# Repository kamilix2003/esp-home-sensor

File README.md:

# esp-home-sensor

Wireless ESP32-C6 based home environmental sensor powered by single Li-ion 18650 cell, running ESP home firmware optimized for battery life which is to be measured in months instead of days.

<figure style="text-align:center;">
  
</figure>

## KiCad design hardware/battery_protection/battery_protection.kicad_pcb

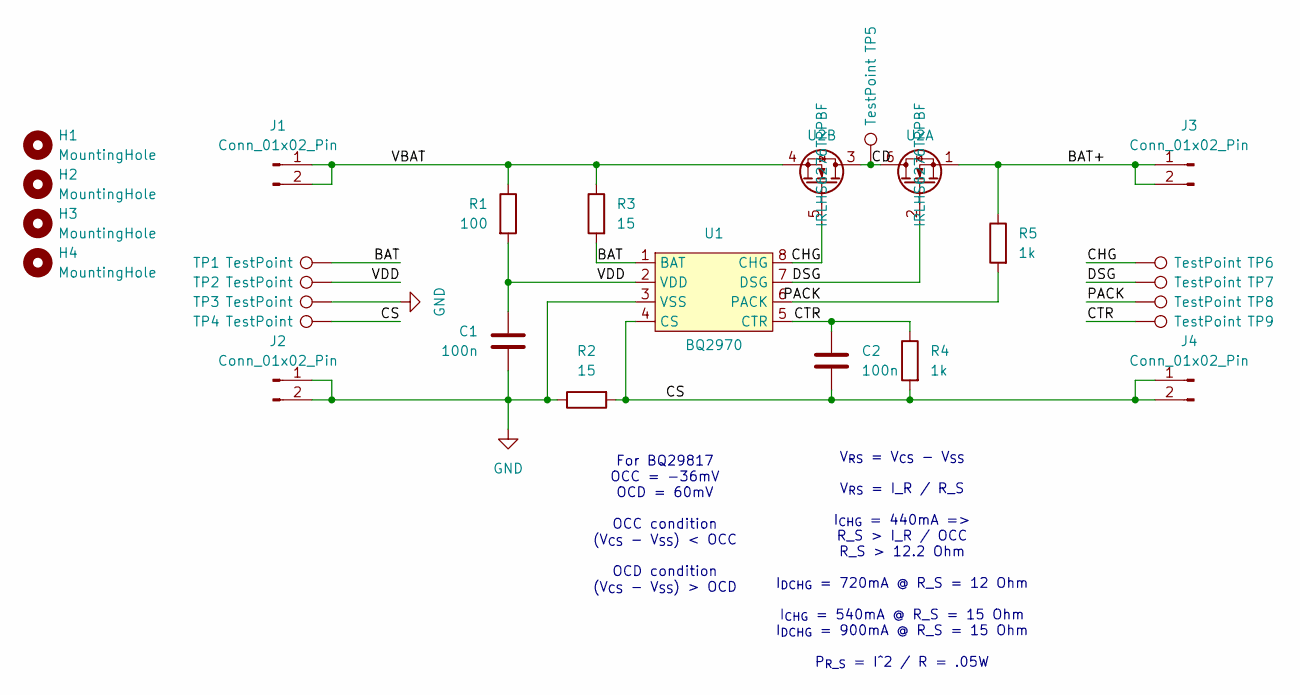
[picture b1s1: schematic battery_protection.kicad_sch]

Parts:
C1, C2: 100n; C_0402_1005Metric
H1, H2, H3, H4: MountingHole; MountingHole_2.2mm_M2
J1, J2, J3, J4: Conn_01x02_Pin; PinHeader_1x02_P2.54mm_Vertical
R1: 100; R_0402_1005Metric
R2, R3: 15; R_0402_1005Metric
R4, R5: 1k; R_0402_1005Metric
TP1, TP2, TP3, TP4, TP5, TP6, TP7, TP8, TP9: TestPoint; TestPoint_THTPad_D1.0mm_Drill0.5mm
U1: BQ2970; QFN-8_1.5x1.5_Pitch0.5mm
U2: IRLHS6276TRPBF; QFN-6_2x2_Pitch0.65mm

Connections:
/BAT: R3.2, TP1.1 (1_1), U1.1 (BAT)
/BAT+: J3.1, J3.2, R5.1, U2.1
/CD: TP5.1 (1_1), U2.3, U2.6
/CHG: TP6.1 (1_1), U1.8 (CHG), U2.5
/CS: C2.2, J4.1, J4.2, R2.2, R4.2, TP4.1 (1_1), U1.4 (CS)
/CTR: C2.1, R4.1, TP9.1 (1_1), U1.5 (CTR)
/DSG: TP7.1 (1_1), U1.7 (DSG), U2.2
/PACK: R5.2, TP8.1 (1_1), U1.6 (PACK)
/VBAT: J1.1, J1.2, R1.1, R3.1, U2.4
/VDD: C1.1, R1.2, TP2.1 (1_1), U1.2 (VDD)
GND: C1.2, J2.1, J2.2, R2.1, TP3.1 (1_1), U1.3 (VSS)

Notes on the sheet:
V_{RS} = V_{CS} - V_{SS} V_{RS} = I_R / R_S I_{CHG} = 440mA => R_S > I_R / OCC R_S > 12.2 Ohm I_{DCHG} = 720mA @ R_S = 12 Ohm I_{CHG} = 540mA @ R_S = 15 Ohm I_{DCHG} = 900mA @ R_S = 15 Ohm P_{R_S} = I^2 / R = .05W
For BQ29817 OCC = -36mV OCD = 60mV OCC condition (V_{CS} - V_{SS}) < OCC OCD condition (V_{CS} - V_{SS}) > OCD

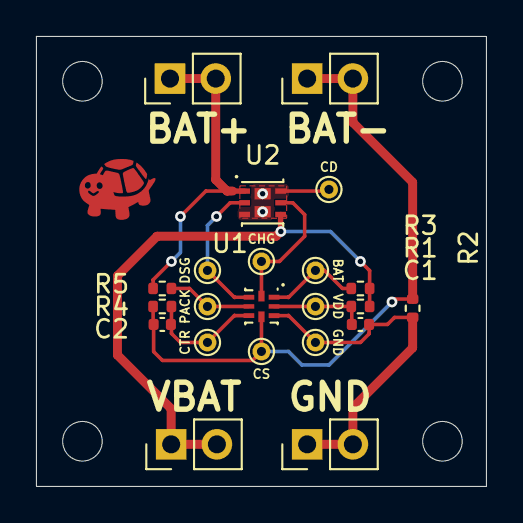
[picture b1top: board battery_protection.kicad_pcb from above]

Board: 2 copper layers, 25.0 x 25.0 mm, 26 parts (0 on the bottom side), 11 nets.

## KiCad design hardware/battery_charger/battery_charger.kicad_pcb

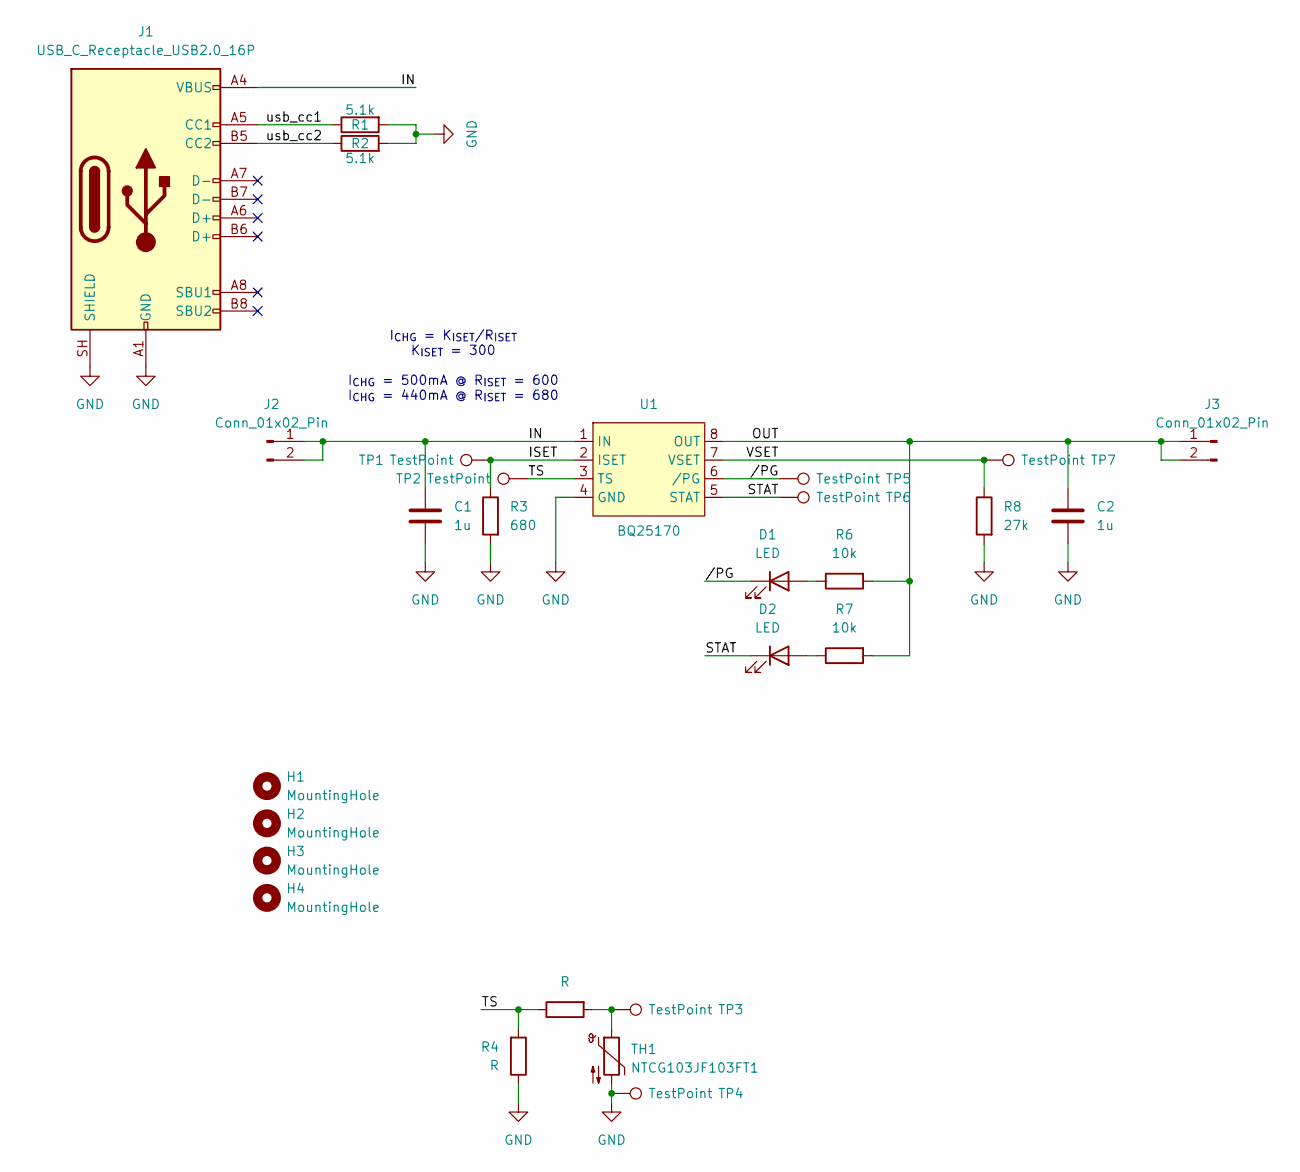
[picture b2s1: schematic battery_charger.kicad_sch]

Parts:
C1, C2: 1u; C_0402_1005Metric
D1, D2: LED; LED_0402_1005Metric
H1, H2, H3, H4: MountingHole; MountingHole_2.2mm_M2
J1: USB_C_Receptacle_USB2.0_16P; USB_C_Receptacle_GCT_USB4110
J2, J3: Conn_01x02_Pin; PinHeader_1x02_P2.54mm_Vertical
R1, R2: 5.1k; R_0402_1005Metric
R3: 680; R_0402_1005Metric
R4, R5: R; R_0402_1005Metric
R6, R7: 10k; R_0402_1005Metric
R8: 27k; R_0402_1005Metric
TH1: NTCG103JF103FT1; R_0603_1608Metric
TP1, TP2, TP3, TP4, TP5, TP6, TP7: TestPoint; TestPoint_THTPad_D1.0mm_Drill0.5mm
U1: BQ25170; QFN-8_EP_2x2_Pitch0.5mm

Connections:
/IN: C1.1, J1.A4 (VBUS), J1.A9 (VBUS), J1.B4 (VBUS), J1.B9 (VBUS), J2.1, J2.2, U1.1 (IN)
/ISET: R3.1, TP1.1 (1_1), U1.2 (ISET)
/OUT: C2.1, J3.1, J3.2, R6.2, R7.2, U1.8 (OUT)
/STAT: D2.1 (K), TP6.1 (1_1), U1.5 (STAT)
/TS: R4.2, R5.1, TP2.1 (1_1), U1.3 (TS)
/VSET: R8.1, TP7.1 (1_1), U1.7 (VSET)
/usb_cc1: J1.A5 (CC1), R1.1
/usb_cc2: J1.B5 (CC2), R2.1
//PG: D1.1 (K), TP5.1 (1_1), U1.6 (/PG)
GND: C1.2, C2.2, J1.A1 (GND), J1.A12 (GND), J1.B1 (GND), J1.B12 (GND), J1.SH (SHIELD), R1.2, R2.2, R3.2, R4.1, R8.2, TH1.2, TP4.1 (1_1), U1.4 (GND)
unnamed: D1.2 (A), R6.1
unnamed: D2.2 (A), R7.1
unnamed: R5.2, TH1.1, TP3.1 (1_1)

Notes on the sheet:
I_{CHG} = K_{ISET}/R_{ISET} K_{ISET} = 300 I_{CHG} = 500mA @ R_{ISET} = 600 I_{CHG} = 440mA @ R_{ISET} = 680

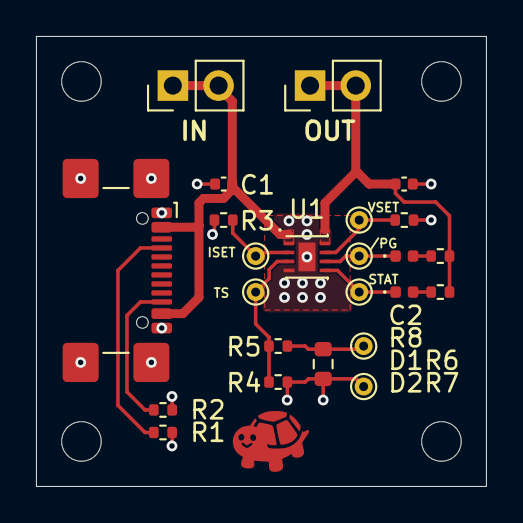
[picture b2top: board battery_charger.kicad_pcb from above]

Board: 2 copper layers, 25.0 x 25.0 mm, 28 parts (0 on the bottom side), 13 nets.

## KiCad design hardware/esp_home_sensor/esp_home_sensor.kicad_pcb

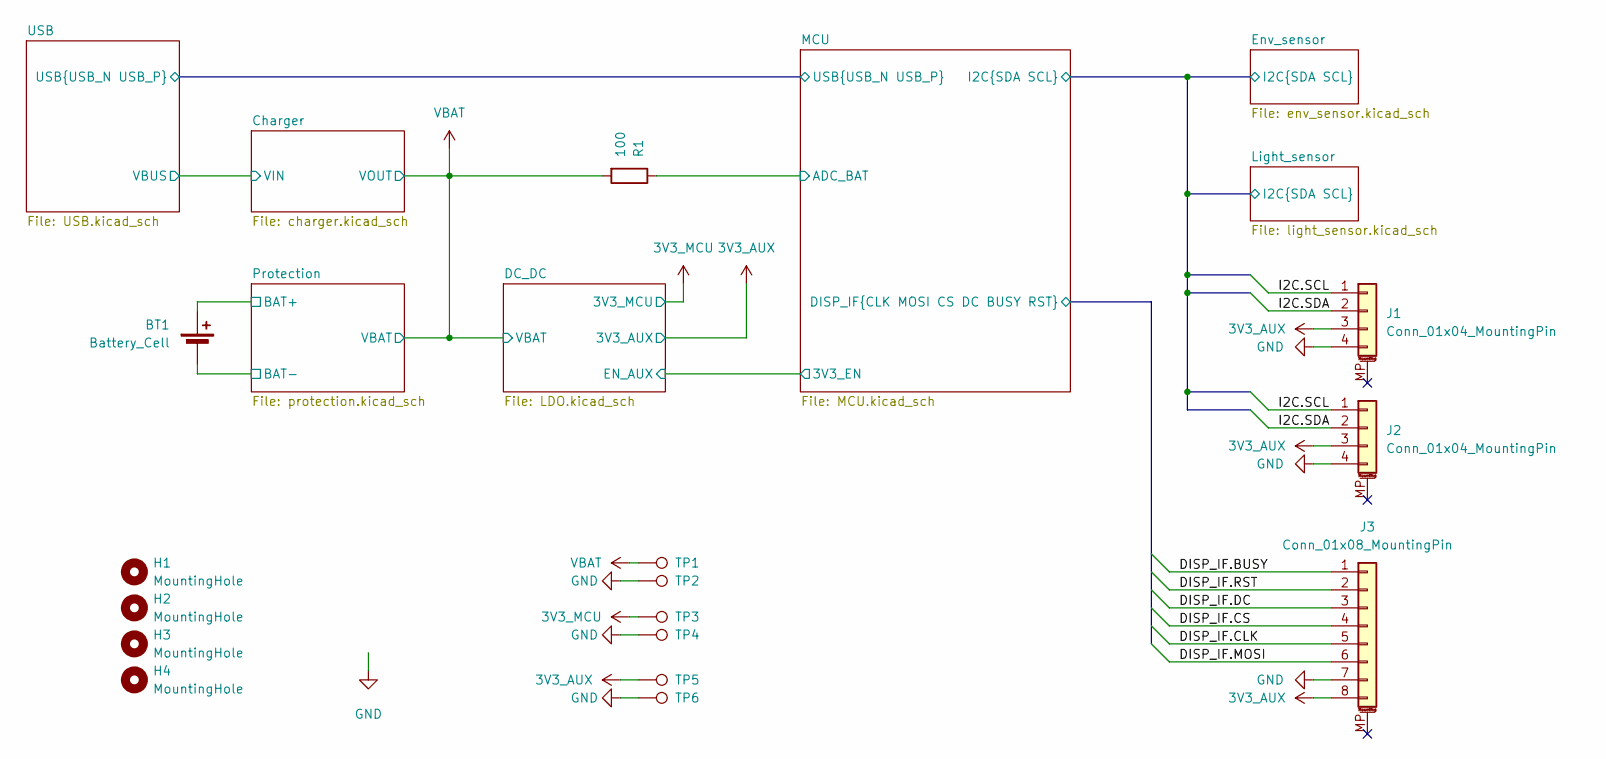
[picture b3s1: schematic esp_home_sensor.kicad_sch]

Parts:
BT1: Battery_Cell
H1, H2, H3, H4: MountingHole; MountingHole_2.2mm_M2
J1, J2: Conn_01x04_MountingPin; JST_SH_SM04B-SRSS-TB_1x04-1MP_P1.00mm_Horizontal
J3: Conn_01x08_MountingPin; JST_SH_SM08B-SRSS-TB_1x08-1MP_P1.00mm_Horizontal
R1: 100; R_0402_1005Metric
TP1, TP2, TP3, TP4, TP5, TP6: TestPoint; TestPoint_Pad_D2.5mm

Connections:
3V3_AUX: J1.3, J2.3, J3.8, TP5.1 (1_1); also elsewhere on the board
3V3_MCU: TP3.1 (1_1); also elsewhere on the board
/Env_sensor/I2C.SCL: J1.1, J2.1; also elsewhere on the board
/Env_sensor/I2C.SDA: J1.2, J2.2; also elsewhere on the board
/MCU/ADC_BAT: R1.1; also elsewhere on the board
/MCU/DISP_IF.BUSY: J3.1; also elsewhere on the board
/MCU/DISP_IF.CLK: J3.5; also elsewhere on the board
/MCU/DISP_IF.CS: J3.4; also elsewhere on the board
/MCU/DISP_IF.DC: J3.3; also elsewhere on the board
/MCU/DISP_IF.MOSI: J3.6; also elsewhere on the board
/MCU/DISP_IF.RST: J3.2; also elsewhere on the board
/Protection/BAT+: BT1.1 (+); also elsewhere on the board
/Protection/BAT-: BT1.2 (-); also elsewhere on the board
GND: J1.4, J2.4, J3.7, TP2.1 (1_1), TP4.1 (1_1), TP6.1 (1_1); also elsewhere on the board
VBAT: R1.2, TP1.1 (1_1); also elsewhere on the board

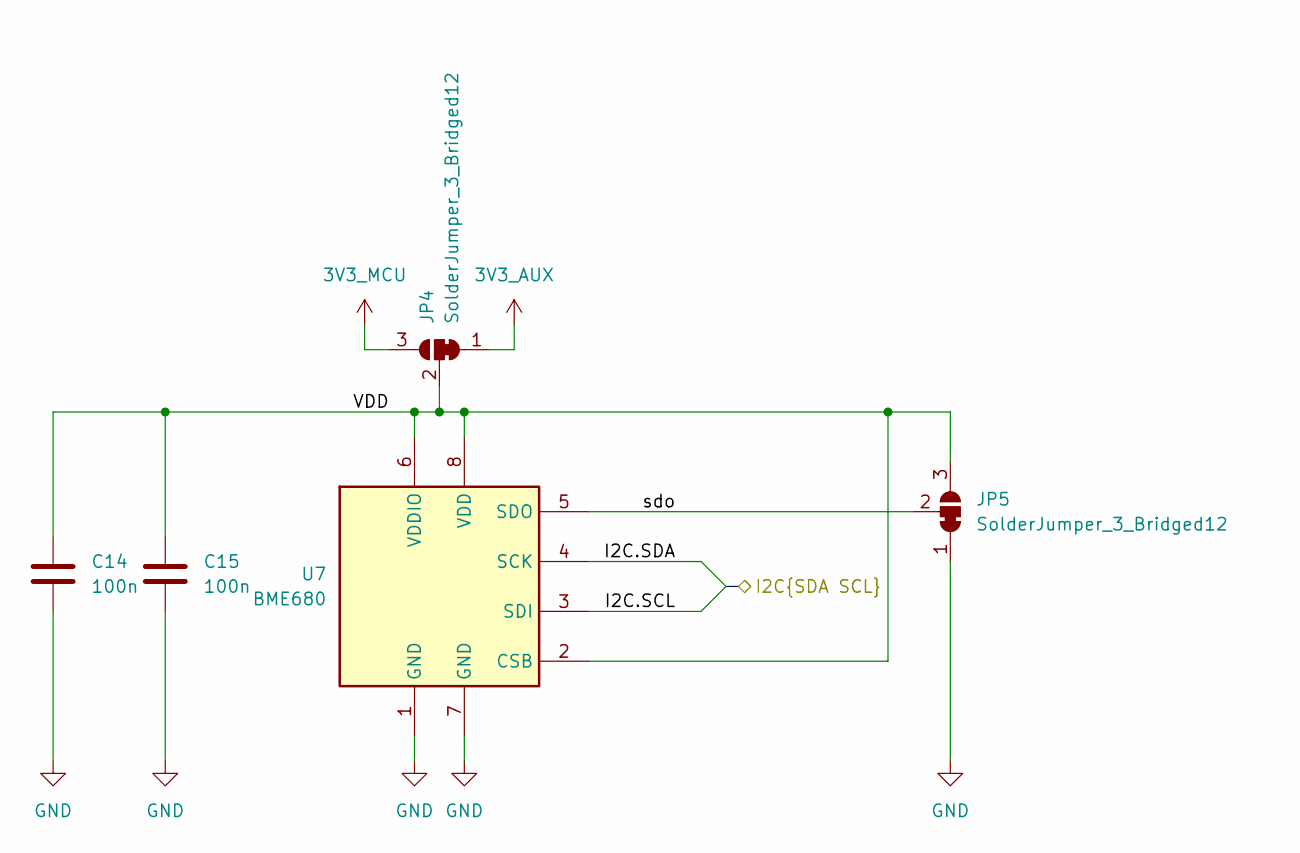
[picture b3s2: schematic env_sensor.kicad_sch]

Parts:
C14, C15: 100n; C_0402_1005Metric
JP4, JP5: SolderJumper_3_Bridged12; SolderJumper-3_P1.3mm_Bridged12_Pad1.0x1.5mm
U7: BME680; Bosch_LGA-8_3x3mm_P0.8mm_ClockwisePinNumbering

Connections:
3V3_AUX: JP4.1 (A); also elsewhere on the board
3V3_MCU: JP4.3 (B); also elsewhere on the board
/Env_sensor/I2C.SCL: U7.3 (SDI); also elsewhere on the board
/Env_sensor/I2C.SDA: U7.4 (SCK); also elsewhere on the board
/Env_sensor/VDD: C14.1, C15.1, JP4.2 (C), JP5.3 (B), U7.2 (CSB), U7.6 (VDDIO), U7.8 (VDD)
/Env_sensor/sdo: JP5.2 (C), U7.5 (SDO)
GND: C14.2, C15.2, JP5.1 (A), U7.1 (GND), U7.7 (GND); also elsewhere on the board

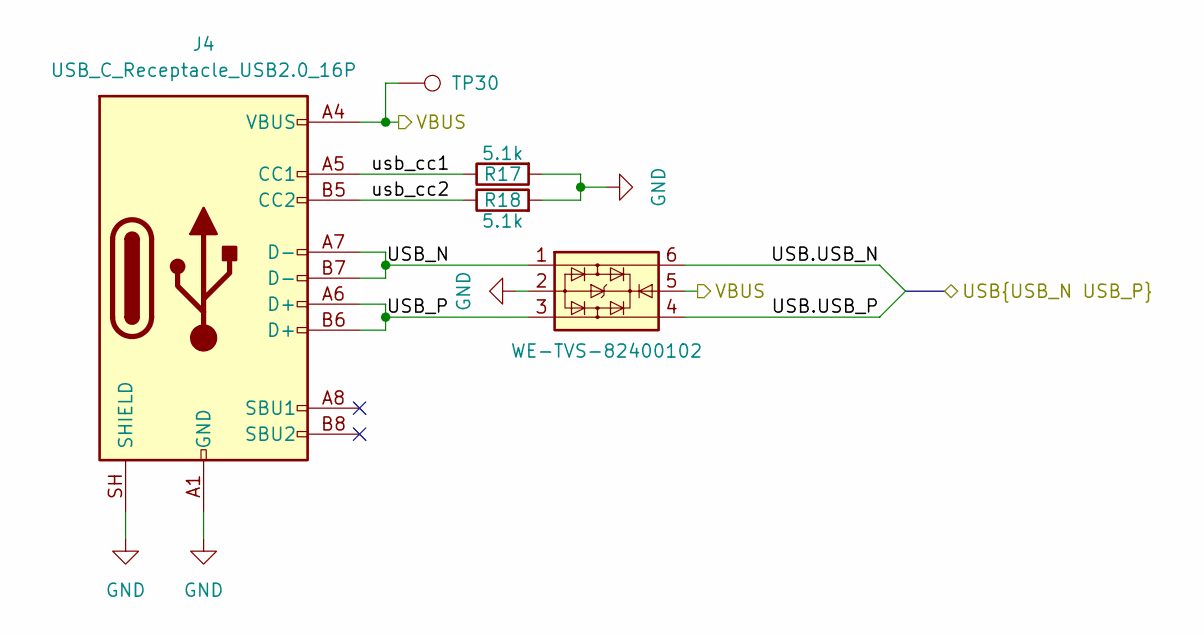
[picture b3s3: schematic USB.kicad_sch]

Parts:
J4: USB_C_Receptacle_USB2.0_16P; USB_C_Receptacle_GCT_USB4110
R17, R18: 5.1k; R_0402_1005Metric
TP30: TestPoint; TestPoint_Pad_D2.5mm
U9: WE-TVS-82400102; SOT-23-6

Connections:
/Charger/VIN: J4.A4 (VBUS), J4.A9 (VBUS), J4.B4 (VBUS), J4.B9 (VBUS), TP30.1 (1_1), U9.5; also elsewhere on the board
/MCU/USB.USB_N: U9.6; also elsewhere on the board
/MCU/USB.USB_P: U9.4; also elsewhere on the board
/USB/USB_N: J4.A7 (D-), J4.B7 (D-), U9.1
/USB/USB_P: J4.A6 (D+), J4.B6 (D+), U9.3
/USB/usb_cc1: J4.A5 (CC1), R17.1
/USB/usb_cc2: J4.B5 (CC2), R18.1
GND: J4.A1 (GND), J4.A12 (GND), J4.B1 (GND), J4.B12 (GND), J4.SH (SHIELD), R17.2, R18.2, U9.2; also elsewhere on the board

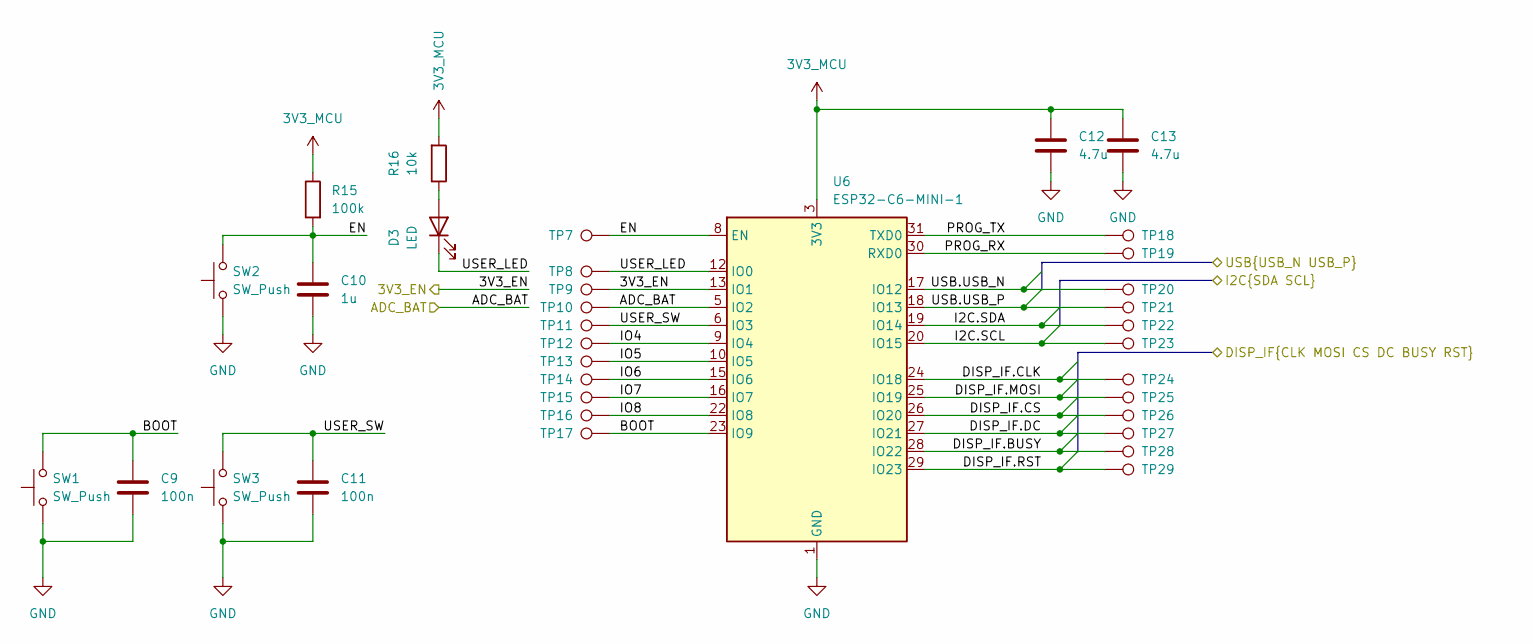
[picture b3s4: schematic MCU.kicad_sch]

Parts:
C9, C11: 100n; C_0402_1005Metric
C10: 1u; C_0402_1005Metric
C12, C13: 4.7u; C_0402_1005Metric
D3: LED; LED_0402_1005Metric
R15: 100k; R_0402_1005Metric
R16: 10k; R_0402_1005Metric
SW1, SW2, SW3: SW_Push; SW_Push_1P1T_NO_CK_KMR2
TP7, TP8, TP9, TP10, TP11, TP12, TP13, TP14, TP15, TP16, TP17, TP18, TP19, TP20, TP21, TP22, TP23, TP24, TP25, TP26, TP27, TP28, TP29: TestPoint; TestPoint_Pad_D1.0mm
U6: ESP32-C6-MINI-1

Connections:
3V3_MCU: C12.1, C13.1, R15.1, R16.2, U6.3 (3V3); also elsewhere on the board
/DC_DC/EN: TP9.1 (1_1), U6.13 (IO1); also elsewhere on the board
/Env_sensor/I2C.SCL: TP23.1 (1_1), U6.20 (IO15); also elsewhere on the board
/Env_sensor/I2C.SDA: TP22.1 (1_1), U6.19 (IO14); also elsewhere on the board
/MCU/ADC_BAT: TP10.1 (1_1), U6.5 (IO2); also elsewhere on the board
/MCU/BOOT: C9.1, SW1.2, TP17.1 (1_1), U6.23 (IO9)
/MCU/DISP_IF.BUSY: TP28.1 (1_1), U6.28 (IO22); also elsewhere on the board
/MCU/DISP_IF.CLK: TP24.1 (1_1), U6.24 (IO18); also elsewhere on the board
/MCU/DISP_IF.CS: TP26.1 (1_1), U6.26 (IO20); also elsewhere on the board
/MCU/DISP_IF.DC: TP27.1 (1_1), U6.27 (IO21); also elsewhere on the board
/MCU/DISP_IF.MOSI: TP25.1 (1_1), U6.25 (IO19); also elsewhere on the board
/MCU/DISP_IF.RST: TP29.1 (1_1), U6.29 (IO23); also elsewhere on the board
/MCU/EN: C10.1, R15.2, SW2.2, TP7.1 (1_1), U6.8 (EN)
/MCU/IO4: TP12.1 (1_1), U6.9 (IO4)
/MCU/IO5: TP13.1 (1_1), U6.10 (IO5)
/MCU/IO6: TP14.1 (1_1), U6.15 (IO6)
/MCU/IO7: TP15.1 (1_1), U6.16 (IO7)
/MCU/IO8: TP16.1 (1_1), U6.22 (IO8)
/MCU/PROG_RX: TP19.1 (1_1), U6.30 (RXD0)
/MCU/PROG_TX: TP18.1 (1_1), U6.31 (TXD0)
/MCU/USB.USB_N: TP20.1 (1_1), U6.17 (IO12); also elsewhere on the board
/MCU/USB.USB_P: TP21.1 (1_1), U6.18 (IO13); also elsewhere on the board
/MCU/USER_LED: D3.1 (K), TP8.1 (1_1), U6.12 (IO0)
/MCU/USER_SW: C11.1, SW3.2, TP11.1 (1_1), U6.6 (IO3)
GND: C9.2, C10.2, C11.2, C12.2, C13.2, SW1.1, SW2.1, SW3.1, U6.1 (GND), U6.2 (GND), U6.11 (GND), U6.14 (GND), U6.36 (GND), U6.37 (GND), U6.38 (GND), U6.39 (GND), U6.40 (GND), U6.41 (GND), U6.42 (GND), U6.43 (GND), U6.44 (GND), U6.45 (GND), U6.46 (GND), U6.47 (GND), U6.48 (GND), U6.49 (GND), U6.50 (GND), U6.51 (GND), U6.52 (GND), U6.53 (GND); also elsewhere on the board
unnamed: D3.2 (A), R16.1

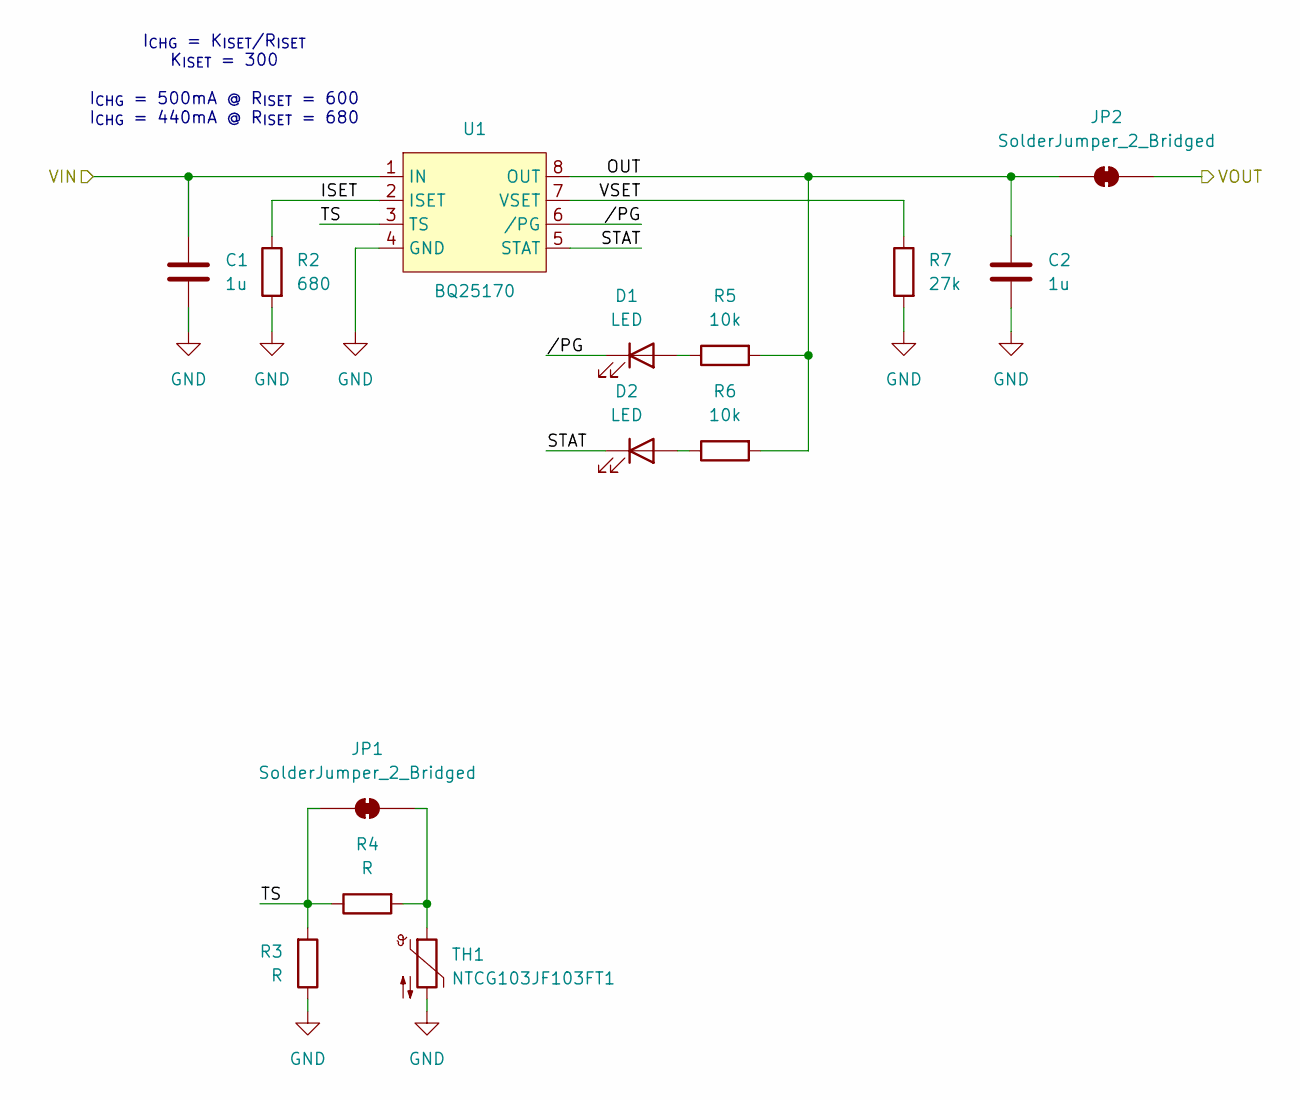
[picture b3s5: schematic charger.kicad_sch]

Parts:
C1, C2: 1u; C_0402_1005Metric
D1, D2: LED; LED_0402_1005Metric
JP1, JP2: SolderJumper_2_Bridged; SolderJumper-2_P1.3mm_Bridged2Bar_Pad1.0x1.5mm
R2: 680; R_0402_1005Metric
R3, R4: R; R_0402_1005Metric
R5, R6: 10k; R_0402_1005Metric
R7: 27k; R_0402_1005Metric
TH1: NTCG103JF103FT1; R_0603_1608Metric
U1: BQ25170; QFN-8_EP_2x2_Pitch0.5mm

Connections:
/Charger/ISET: R2.1, U1.2 (ISET)
/Charger/OUT: C2.1, JP2.1 (A), R5.2, R6.2, U1.8 (OUT)
/Charger/STAT: D2.1 (K), U1.5 (STAT)
/Charger/TS: JP1.1 (A), R3.2, R4.1, U1.3 (TS)
/Charger/VIN: C1.1, U1.1 (IN); also elsewhere on the board
/Charger/VSET: R7.1, U1.7 (VSET)
/Charger//PG: D1.1 (K), U1.6 (/PG)
GND: C1.2, C2.2, R2.2, R3.1, R7.2, TH1.2, U1.4 (GND); also elsewhere on the board
unnamed: D1.2 (A), R5.1
unnamed: D2.2 (A), R6.1
unnamed: JP1.2 (B), R4.2, TH1.1
VBAT: JP2.2 (B); also elsewhere on the board

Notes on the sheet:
I_{CHG} = K_{ISET}/R_{ISET} K_{ISET} = 300 I_{CHG} = 500mA @ R_{ISET} = 600 I_{CHG} = 440mA @ R_{ISET} = 680

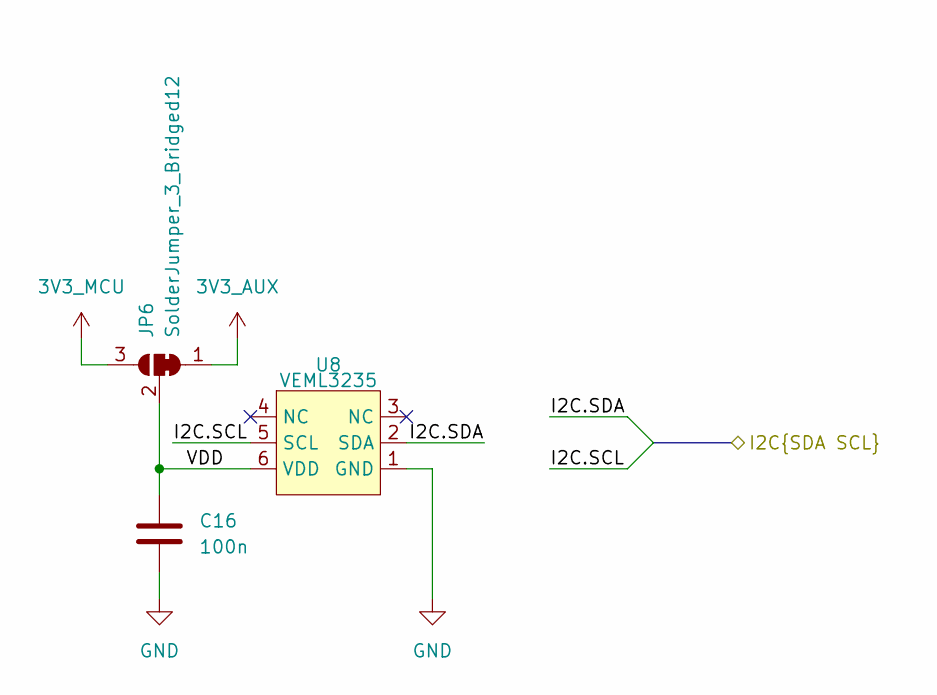
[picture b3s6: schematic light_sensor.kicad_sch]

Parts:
C16: 100n; C_0402_1005Metric
JP6: SolderJumper_3_Bridged12; SolderJumper-3_P1.3mm_Bridged12_Pad1.0x1.5mm
U8: VEML3235

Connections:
3V3_AUX: JP6.1 (A); also elsewhere on the board
3V3_MCU: JP6.3 (B); also elsewhere on the board
/Env_sensor/I2C.SCL: U8.5 (SCL); also elsewhere on the board
/Env_sensor/I2C.SDA: U8.2 (SDA); also elsewhere on the board
/Light_sensor/VDD: C16.1, JP6.2 (C), U8.6 (VDD)
GND: C16.2, U8.1 (GND); also elsewhere on the board

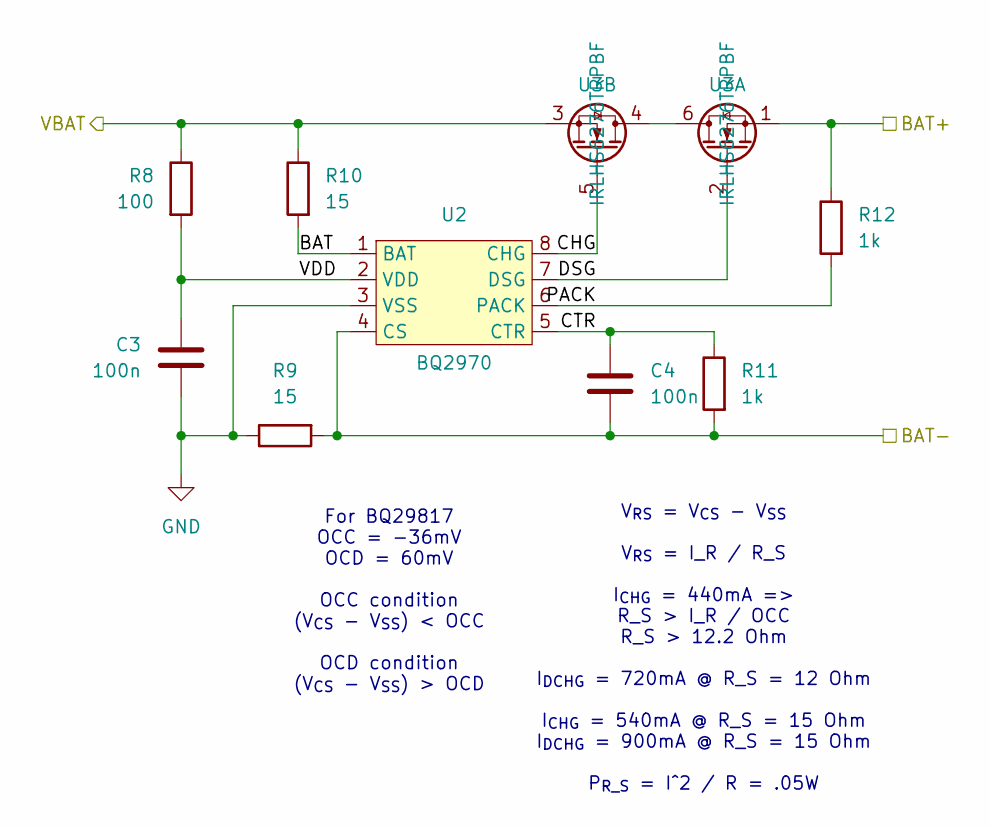
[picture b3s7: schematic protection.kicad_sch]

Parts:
C3, C4: 100n; C_0402_1005Metric
R8: 100; R_0402_1005Metric
R9, R10: 15; R_0402_1005Metric
R11, R12: 1k; R_0402_1005Metric
U2: BQ2970; QFN-8_1.5x1.5_Pitch0.5mm
U3: IRLHS6276TRPBF; QFN-6_2x2_Pitch0.65mm

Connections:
/Protection/BAT: R10.2, U2.1 (BAT)
/Protection/BAT+: R12.1, U3.1; also elsewhere on the board
/Protection/BAT-: C4.2, R9.2, R11.2, U2.4 (CS); also elsewhere on the board
/Protection/CHG: U2.8 (CHG), U3.5
/Protection/CTR: C4.1, R11.1, U2.5 (CTR)
/Protection/DSG: U2.7 (DSG), U3.2
/Protection/PACK: R12.2, U2.6 (PACK)
/Protection/VDD: C3.1, R8.2, U2.2 (VDD)
GND: C3.2, R9.1, U2.3 (VSS); also elsewhere on the board
unnamed: U3.4, U3.6
VBAT: R8.1, R10.1, U3.3; also elsewhere on the board

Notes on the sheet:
V_{RS} = V_{CS} - V_{SS} V_{RS} = I_R / R_S I_{CHG} = 440mA => R_S > I_R / OCC R_S > 12.2 Ohm I_{DCHG} = 720mA @ R_S = 12 Ohm I_{CHG} = 540mA @ R_S = 15 Ohm I_{DCHG} = 900mA @ R_S = 15 Ohm P_{R_S} = I^2 / R = .05W
For BQ29817 OCC = -36mV OCD = 60mV OCC condition (V_{CS} - V_{SS}) < OCC OCD condition (V_{CS} - V_{SS}) > OCD

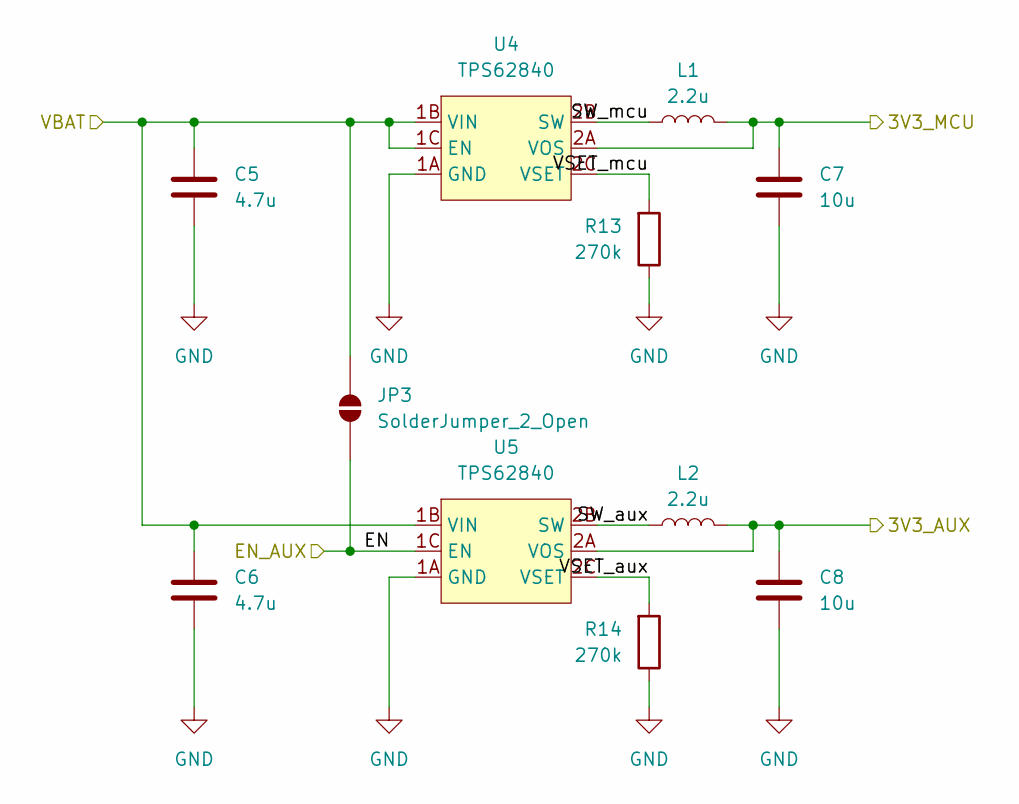
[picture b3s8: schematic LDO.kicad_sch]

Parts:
C5, C6: 4.7u; C_0402_1005Metric
C7, C8: 10u; C_0402_1005Metric
JP3: SolderJumper_2_Open; SolderJumper-2_P1.3mm_Open_Pad1.0x1.5mm
L1, L2: 2.2u; L_0805_2012Metric
R13, R14: 270k; R_0402_1005Metric
U4, U5: TPS62840; BGA-6_2x3_1.5x1.2mm

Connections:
3V3_AUX: C8.1, L2.2, U5.2A (VOS); also elsewhere on the board
3V3_MCU: C7.1, L1.2, U4.2A (VOS); also elsewhere on the board
/DC_DC/EN: JP3.1 (A), U5.1C (EN); also elsewhere on the board
/DC_DC/SW_aux: L2.1, U5.2B (SW)
/DC_DC/SW_mcu: L1.1, U4.2B (SW)
/DC_DC/VSET_aux: R14.2, U5.2C (VSET)
/DC_DC/VSET_mcu: R13.2, U4.2C (VSET)
GND: C5.2, C6.2, C7.2, C8.2, R13.1, R14.1, U4.1A (GND), U5.1A (GND); also elsewhere on the board
VBAT: C5.1, C6.1, JP3.2 (B), U4.1B (VIN), U4.1C (EN), U5.1B (VIN); also elsewhere on the board

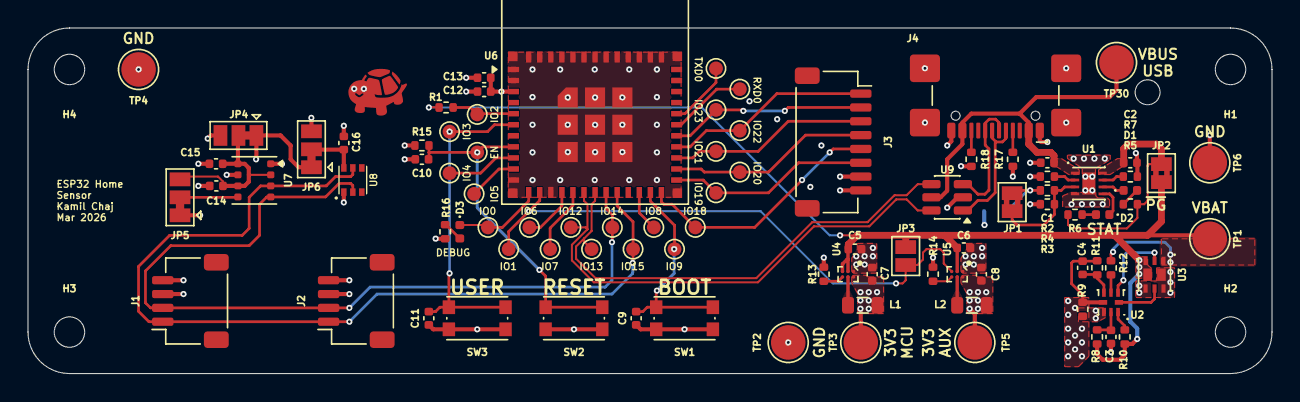
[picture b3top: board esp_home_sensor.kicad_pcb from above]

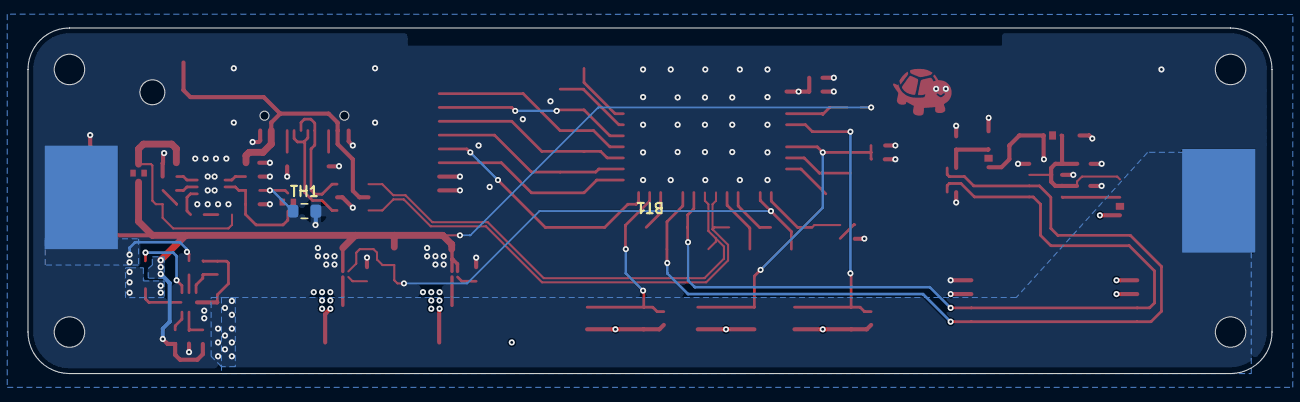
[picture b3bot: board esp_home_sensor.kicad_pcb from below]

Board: 4 copper layers, 90.0 x 25.0 mm, 97 parts (2 on the bottom side), 58 nets.

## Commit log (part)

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2026-03-20 init kicad
2026-03-20 schematic
2026-03-21 busses, display connector, footprint lib
2026-03-23 footprint assignment, buck
2026-03-23 minor update
2026-03-26 initial layout, power routing
2026-03-29 layout
2026-03-30 tutel
2026-04-01 in production
